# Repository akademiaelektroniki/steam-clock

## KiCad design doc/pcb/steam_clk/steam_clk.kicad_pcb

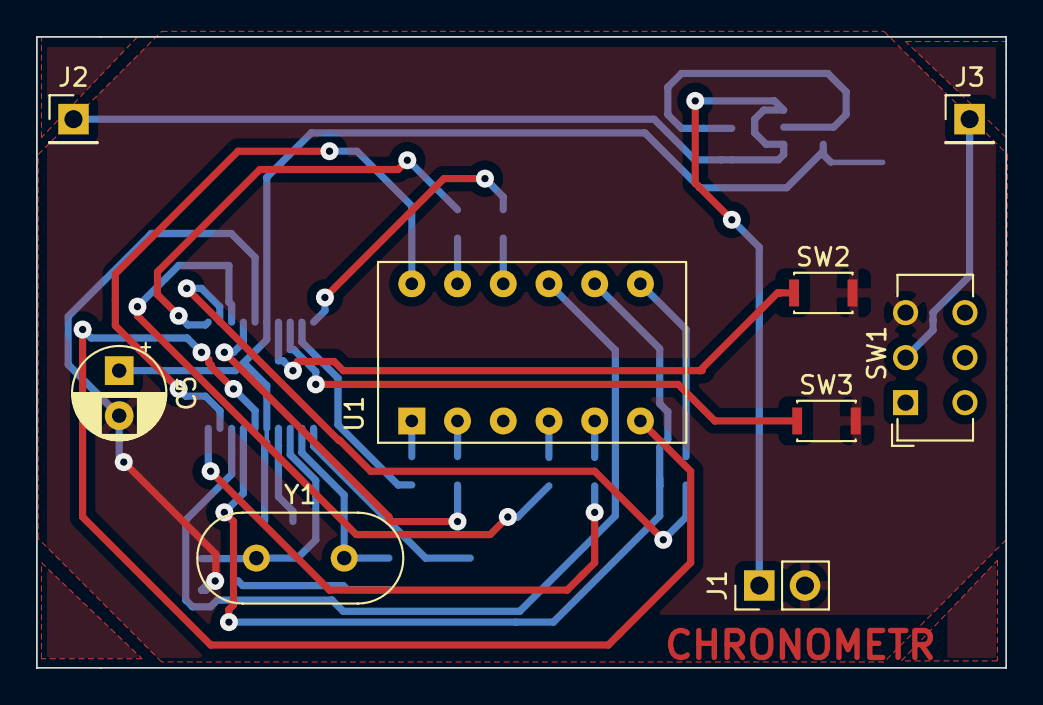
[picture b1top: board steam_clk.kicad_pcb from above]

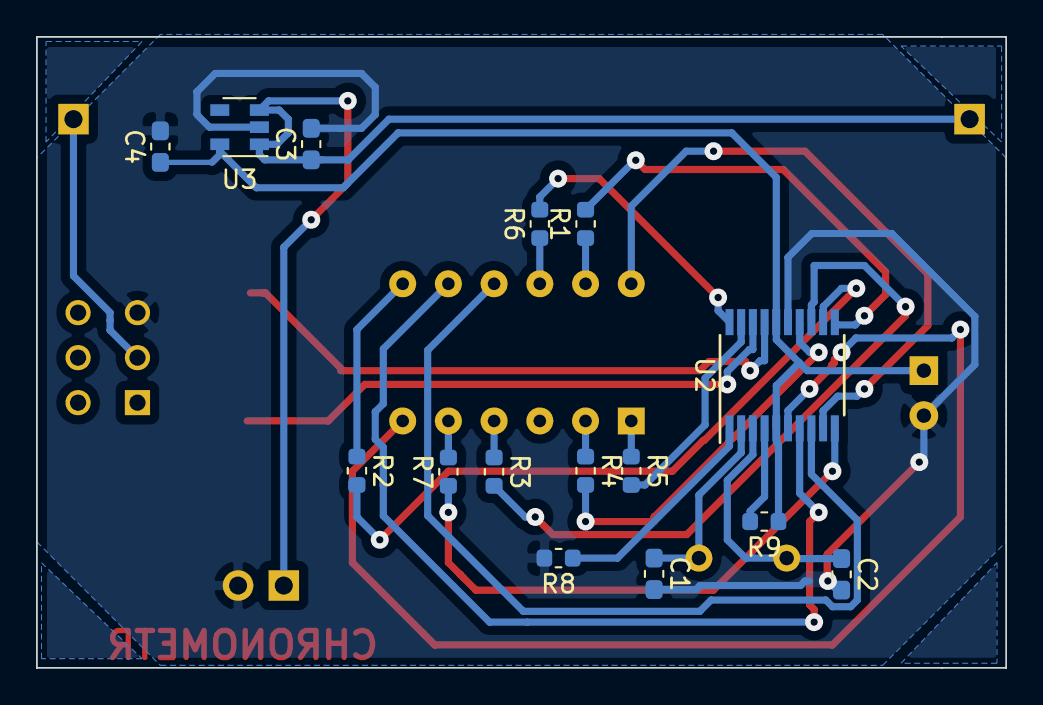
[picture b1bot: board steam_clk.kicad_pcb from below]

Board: 2 copper layers, 53.8 x 35.1 mm, 24 parts (15 on the bottom side), 28 nets.

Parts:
C1, C2: 22p; C_0603_1608Metric_Pad1.05x0.95mm_HandSolder
C3, C4: 100n; C_0603_1608Metric_Pad1.05x0.95mm_HandSolder
C5: 100u; CP_Radial_D5.0mm_P2.50mm
J1: Goldpin; PinHeader_1x02_P2.54mm_Vertical
J2: Cell+; PinHeader_1x01_P2.54mm_Vertical
J3: Cell-; PinHeader_1x01_P2.54mm_Vertical
R1, R2, R3, R4, R5, R6, R7: 120; R_0603_1608Metric
R8, R9: 10k; R_0603_1608Metric
SW1: POWER; SW_CuK_JS202011CQN_DPDT_Straight
SW2: SET; SW_SPST_CK_KXT3
SW3: CLEAR; SW_SPST_CK_KXT3
U1: BQ-M322RD; MAN3420A
U2: STM32F030F4Px; TSSOP-20_4.4x6.5mm_P0.65mm
U3: TC1185-3.3VCT8; SOT-23-5
Y1: 18.432MHz; Crystal_HC49-4H_Vertical

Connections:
+3V3: C4.1, C5.1, R9.1, U2.5, U2.16, U3.5
D1: U1.12, U2.9
D2: U1.9, U2.8
D3: U1.8, U2.7
D4: U1.6, U2.6
GND: C1.2, C2.2, C3.2, C4.2, C5.2, J1.2, R8.2, SW1.3, SW2.2, SW3.2, U2.15, U3.2
unnamed: C1.1, U2.2, Y1.2
unnamed: C2.1, U2.3, Y1.1
unnamed: C3.1, J1.1, J2.1, U3.1, U3.3
unnamed: J3.1, SW1.2
unnamed: R1.1, U1.11
unnamed: R2.1, U1.7
unnamed: R3.1, U1.4
unnamed: R4.1, U1.2
unnamed: R5.1, U1.1
unnamed: R6.1, U1.10
unnamed: R7.2, U1.5
unnamed: R8.1, U2.1
unnamed: R9.2, U2.4
unnamed: SW2.1, U2.17
unnamed: SW3.1, U2.18
SA: R1.2, U2.11
SB: R2.2, U2.12
SC: R3.2, U2.13
SD: R4.2, U2.14
SE: R5.2, U2.19
SF: R6.2, U2.20
SG: R7.1, U2.10

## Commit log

2019-07-09 initial
2019-07-10 zmiana nazwy dokumentacji
2019-07-11 added PCB to license
2019-07-12 added name on PCB
2019-07-12 added places for cage
2019-07-13 scheme
2019-07-15 better tracks on pcb
2019-07-15 todo + plany na wersję daily
2019-07-15 dodana wersja daily, uaktualnione footprinty przycisków
2019-07-15 atomic board
2019-07-15 atomic
2019-07-15 atomic update
2019-07-16 przygotowanie pod nowy akumulator
2019-07-16 jst conetor
2019-07-16 better colors
2019-07-17 better pathm replaced uc
2019-07-17 zminimalizowana ilość przelotek
2019-07-18 correct pads for battery
2019-07-18 updated to 7,3728 quartz
2019-07-18 fully functional ondemand mode with menu option
2019-07-21 folder name changes
2019-07-22 better pad
